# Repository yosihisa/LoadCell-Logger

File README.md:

# LoadCell-Logger
4ch load cell logger board using Raspberry Pi Pico and HX711.  (Wakame Edition)

# ロードセルロガー
HX711とRaspberry Pi Picoを使用した4チャンネルロードセルロガーです。

# ソフトウェア開発環境

## 必要なもの
- Arduino IDE  
- 追加ボード [earlephilhower/arduino-pico](https://github.com/earlephilhower/arduino-pico) 

 Arduino公式のライブラリではマルチコアを使えないためこちら使用する。

## 設定方法 (環境構築)

### ①ボードの準備
ArduinoIDEの「ファイル」>「環境設定」から「追加のボードマネージャのURL」を開き以下のURLを追加する。
> https://github.com/earlephilhower/arduino-pico/releases/download/global/package_rp2040_index.json

ArduinoIDEの「ツール」> 「ボード」> 「ボードマネージャ」から `Raspberry Pi Pico/RP2040` をインストールする。

### ②ボードの設定  
ArduinoIDEから次のボードを設定する。  
`ボード` > `Raspberry Pi RP2040 Boards` > `Raspberry Pi Pico`  

コンパイルオプションは標準のままでよい。  
(Flash Size :2MB(noFS) , CPU Speed :125MHz , 各種デバッグ: 無効 , USB Stack: Pico SDK)

# 使い方 (暫定版)
## 必要なもの
- ソフト
  - TeraTermや[SerialMonitorEssential](https://github.com/771-8bit/SerialMonitorEssential)のようなシリアルモニタ

- ハード  
  - ロードセル
    - 基板上の端子台の表記を参考に接続する。色の意味は以下の通り。
        - 赤 : 印加電圧+
        - 黒 : 印加電圧-
        - 緑 : 出力信号+
        - 白 : 出力信号ｰ
  - USBケーブル
    - PCと接続する。電源もUSB経由で給電される。

## 使い方
1. LoadCell-Logger本体とPCをUSBで接続しシリアルモニタを起動する。  
   baudrate : 115200bps
2. シリアルモニタにカンマ区切りの12列のデータが自動で送られてくる。
   各データは左から1chから4chの順に並んでいる。
   - 1～4列目　ADC出力の生の値
   - 5～8列目　[gf]に換算した荷重　変換係数は[LoadCell-Logger.ino](src\LoadCell-Logger\LoadCell-Logger.ino)の先頭で定義されている。
   - 9～12列目　前回の表示から計測が更新された回数。1ならば正常。2以上の場合は読み飛ばしが発生している。
   - 13列目　外部出力信号の状態
   - 更新間隔　100Hz(10ms)ごとに1回(1行)更新される。
3. Aボタンを押すとオフセット調整ができる。
   - Aボタンを押した瞬間の値が原点として認識される。
   - ロードセルを荷重0の状態にしてAボタンを押すことで原点の調整が完了する。
4. シリアルモニタの機能を使用してログを記録する。
   - カンマ区切りのデータが出力されるので、そのままcsvファイルとして保存できる。

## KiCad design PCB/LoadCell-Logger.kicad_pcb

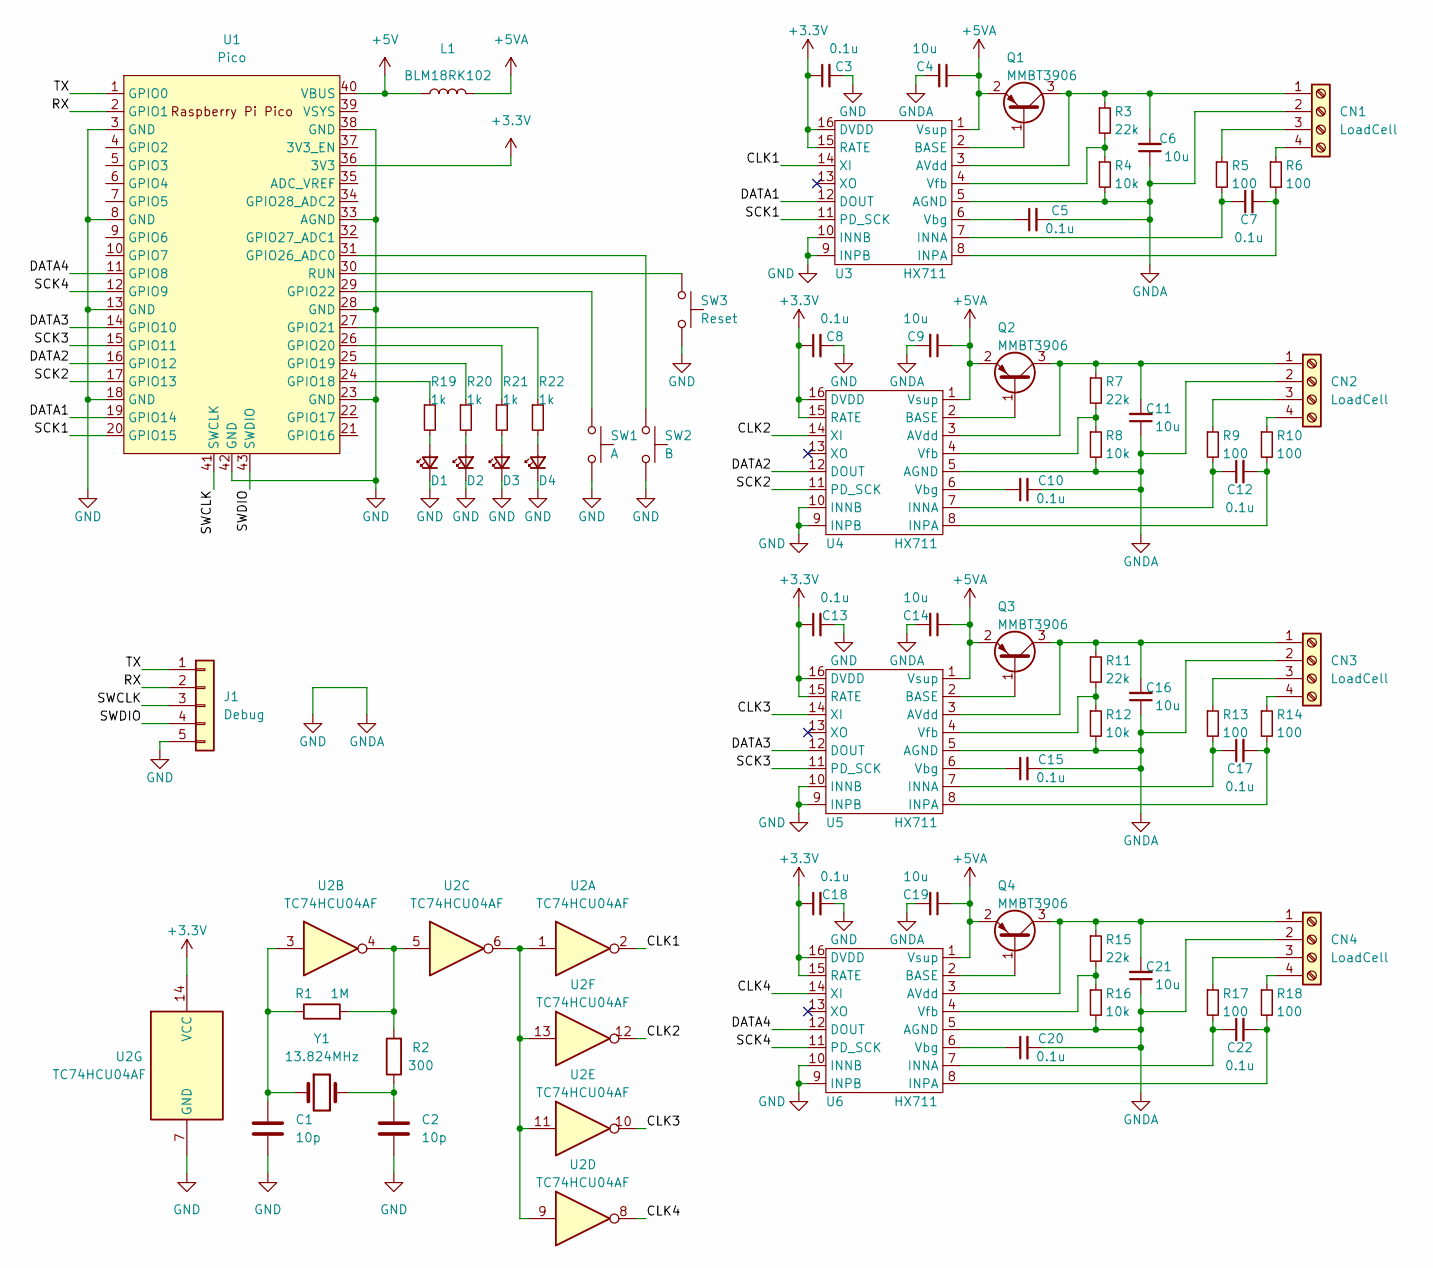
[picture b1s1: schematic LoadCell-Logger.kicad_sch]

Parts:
C1, C2: 10p; C_0603_1608Metric_Pad1.08x0.95mm_HandSolder
C3, C5, C7, C8, C10, C12, C13, C15, C17, C18, C20, C22: 0.1u; C_0603_1608Metric_Pad1.08x0.95mm_HandSolder
C4, C6, C9, C11, C14, C16, C19, C21: 10u; C_0805_2012Metric_Pad1.18x1.45mm_HandSolder
CN1, CN2, CN3, CN4: LoadCell; Molex_SPOX_5268-04A_1x04_P2.50mm_Horizontal
D1, D2, D3, D4: LED; LED_0603_1608Metric_Pad1.05x0.95mm_HandSolder
J1: Debug; STlink
L1: BLM18RK102; L_0603_1608Metric_Pad1.05x0.95mm_HandSolder
Q1, Q2, Q3, Q4: MMBT3906; SOT-23
R1: 1M; R_0805_2012Metric_Pad1.20x1.40mm_HandSolder
R2: 300; R_0603_1608Metric_Pad0.98x0.95mm_HandSolder
R3, R7, R11, R15: 22k; R_0603_1608Metric_Pad0.98x0.95mm_HandSolder
R4, R8, R12, R16: 10k; R_0603_1608Metric_Pad0.98x0.95mm_HandSolder
R5, R6, R9, R10, R13, R14, R17, R18: 100; R_0603_1608Metric_Pad0.98x0.95mm_HandSolder
R19, R20, R21, R22: 1k; R_0603_1608Metric_Pad0.98x0.95mm_HandSolder
SW1: A; SKRPACE010_kai
SW2: B; SKRPACE010_kai
SW3: Reset; SKRPACE010_kai
U1: Pico; RPi_Pico_SMD_TH
U2: TC74HCU04AF; SO-14_5.3x10.2mm_P1.27mm
U3, U4, U5, U6: HX711; SOP-16_3.9x9.9mm_P1.27mm
Y1: 13.824MHz; Crystal_HC49-U_Vertical

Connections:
+3V3: C3.1, C8.1, C13.1, C18.1, U1.36 (3V3), U2.14 (VCC), U3.15 (RATE), U3.16 (DVDD), U4.15 (RATE), U4.16 (DVDD), U5.15 (RATE), U5.16 (DVDD), U6.15 (RATE), U6.16 (DVDD)
+5V: L1.1, U1.40 (VBUS)
+5VA: C4.1, C9.1, C14.1, C19.1, L1.2, Q1.2 (E), Q2.2 (E), Q3.2 (E), Q4.2 (E), U3.1 (Vsup), U4.1 (Vsup), U5.1 (Vsup), U6.1 (Vsup)
/CLK1: U2.2, U3.14 (XI)
/CLK2: U2.12, U4.14 (XI)
/CLK3: U2.10, U5.14 (XI)
/CLK4: U2.8, U6.14 (XI)
/DATA1: U1.19 (GPIO14), U3.12 (DOUT)
/DATA2: U1.16 (GPIO12), U4.12 (DOUT)
/DATA3: U1.14 (GPIO10), U5.12 (DOUT)
/DATA4: U1.11 (GPIO8), U6.12 (DOUT)
/RX: J1.2, U1.2 (GPIO1)
/SCK1: U1.20 (GPIO15), U3.11 (PD_SCK)
/SCK2: U1.17 (GPIO13), U4.11 (PD_SCK)
/SCK3: U1.15 (GPIO11), U5.11 (PD_SCK)
/SCK4: U1.12 (GPIO9), U6.11 (PD_SCK)
/SWCLK: J1.3, U1.41 (SWCLK)
/SWDIO: J1.4, U1.43 (SWDIO)
/TX: J1.1, U1.1 (GPIO0)
GND: C1.2, C2.2, C3.2, C4.2, C5.2, C6.1, C8.2, C9.2, C10.2, C11.1, C13.2, C14.2, C15.2, C16.1, C18.2, C19.2, C20.2, C21.1, CN1.2, CN2.2, CN3.2, CN4.2, D1.1 (K), D2.1 (K), D3.1 (K), D4.1 (K), J1.5, R4.2, R8.2, R12.2, R16.2, SW1.2, SW2.2, SW3.2, U1.3 (GND), U1.8 (GND), U1.13 (GND), U1.18 (GND), U1.23 (GND), U1.28 (GND), U1.33 (AGND), U1.38 (GND), U1.42 (GND), U2.7 (GND), U3.5 (AGND), U3.9 (INPB), U3.10 (INNB), U4.5 (AGND), U4.9 (INPB), U4.10 (INNB), U5.5 (AGND), U5.9 (INPB), U5.10 (INNB), U6.5 (AGND), U6.9 (INPB), U6.10 (INNB)
unnamed: C1.1, R1.1, U2.3, Y1.1
unnamed: C2.1, R2.1, Y1.2
unnamed: C5.1, U3.6 (Vbg)
unnamed: C6.2, CN1.1, Q1.3 (C), R3.1, U3.3 (AVdd)
unnamed: C7.1, R5.2, U3.7 (INNA)
unnamed: C7.2, R6.2, U3.8 (INPA)
unnamed: C10.1, U4.6 (Vbg)
unnamed: C11.2, CN2.1, Q2.3 (C), R7.1, U4.3 (AVdd)
unnamed: C12.1, R9.2, U4.7 (INNA)
unnamed: C12.2, R10.2, U4.8 (INPA)
unnamed: C15.1, U5.6 (Vbg)
unnamed: C16.2, CN3.1, Q3.3 (C), R11.1, U5.3 (AVdd)
unnamed: C17.1, R13.2, U5.7 (INNA)
unnamed: C17.2, R14.2, U5.8 (INPA)
unnamed: C20.1, U6.6 (Vbg)
unnamed: C21.2, CN4.1, Q4.3 (C), R15.1, U6.3 (AVdd)
unnamed: C22.1, R17.2, U6.7 (INNA)
unnamed: C22.2, R18.2, U6.8 (INPA)
unnamed: CN1.3, R5.1
unnamed: CN1.4, R6.1
unnamed: CN2.3, R9.1
unnamed: CN2.4, R10.1
unnamed: CN3.3, R13.1
unnamed: CN3.4, R14.1
unnamed: CN4.3, R17.1
unnamed: CN4.4, R18.1
unnamed: D1.2 (A), R19.2
unnamed: D2.2 (A), R20.2
unnamed: D3.2 (A), R21.2
unnamed: D4.2 (A), R22.2
unnamed: Q1.1 (B), U3.2 (BASE)
unnamed: Q2.1 (B), U4.2 (BASE)
unnamed: Q3.1 (B), U5.2 (BASE)
unnamed: Q4.1 (B), U6.2 (BASE)
unnamed: R1.2, R2.2, U2.4, U2.5
unnamed: R3.2, R4.1, U3.4 (Vfb)
unnamed: R7.2, R8.1, U4.4 (Vfb)
unnamed: R11.2, R12.1, U5.4 (Vfb)
unnamed: R15.2, R16.1, U6.4 (Vfb)
unnamed: R19.1, U1.24 (GPIO18)
unnamed: R20.1, U1.25 (GPIO19)
unnamed: R21.1, U1.26 (GPIO20)
unnamed: R22.1, U1.27 (GPIO21)
unnamed: SW1.1, U1.29 (GPIO22)
unnamed: SW2.1, U1.31 (GPIO26_ADC0)
unnamed: SW3.1, U1.30 (RUN)
unnamed: U2.1, U2.6, U2.9, U2.11, U2.13

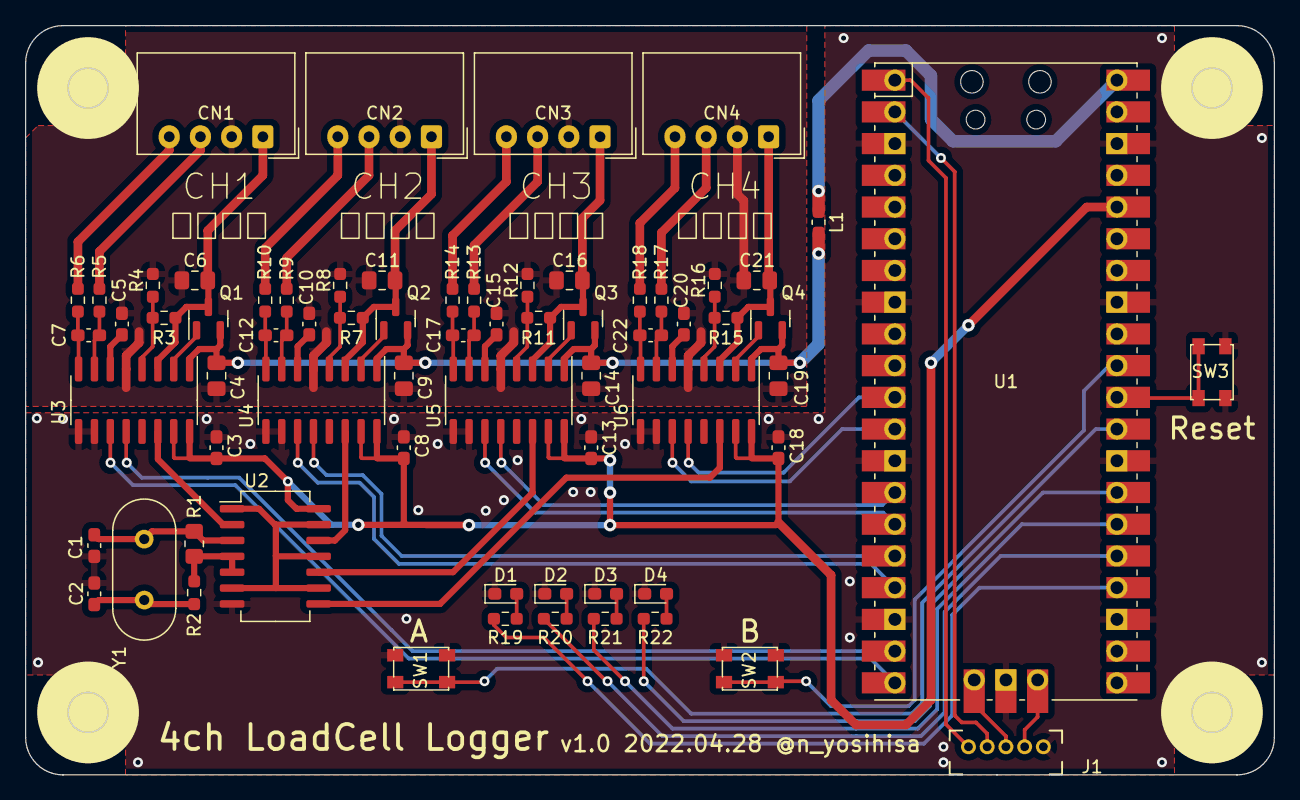
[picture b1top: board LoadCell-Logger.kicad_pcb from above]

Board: 2 copper layers, 100.0 x 60.0 mm, 68 parts (0 on the bottom side), 67 nets.

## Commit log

2022-04-23 基板設計完了(初回)
2022-04-23 部品配置
2022-04-25 ロガー側配線完了
2022-04-28 基板設計完了
2022-04-28 最初の設計 (#1)
2022-12-17 デバッガー削除
2022-12-17 Revert "最初の設計 (#1)"
    This reverts commit 564b5e93a8b9a305720cbd9d862d9edbbbe04bbe.
2023-11-13 使い方(暫定版)追記
2024-07-28 同期用信号出力に対応
